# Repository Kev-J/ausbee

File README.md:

Overview
============

Architecture Using STM32 By Eirbot ENSEIRB-MATMECA.
This tool is provided for building automatically a complete STM32F project.

Licence
=============

See LICENCE file.

Usage
=============

- git clone the repository or download the snapshot of the last version.
- If you choose the git clone method, it is recommended to use a tagged version (git checkout vX.X).
- Configure your board (type "make help" for further informations).
- write your source code in Project/src (headers and source files).
- run "make"
- run "make program" for downloading your code into your device.

For further informations, please visit our wiki : https://github.com/Kev-J/ausbee/wiki

Features
=============

- FreeRTOS
- ST Std_Periph_Driver
- libausbee
- stm32flash

Dependencies
=============
* gperf
* flex
* bison
* libncurses-dev (for menuconfig)
* wget
* unzip
* tar
* stm32flash

Please note that this project is using many third party programs. Please ensure
that your setup have all the requirements before using them. For instance,
have a look to the [GCC arm embedded README](https://launchpadlibrarian.net/209775724/readme.txt)
and check that you have all the dependencies installed on your machine before
trying to compile anything.

Authors of the project
=============

Please see AUTHORS

Bugs, patch, requests
=============

https://github.com/Kev-J/ausbee
or
<ausbee@googlegroups.com>

Maintainer : Kevin JOLY <joly.kevin25@gmail.com>

Related to this project
=============

libausbee
-------------
https://github.com/Kev-J/libausbee

ausbee-hardware
-------------
https://github.com/Kev-J/ausbee-hardware

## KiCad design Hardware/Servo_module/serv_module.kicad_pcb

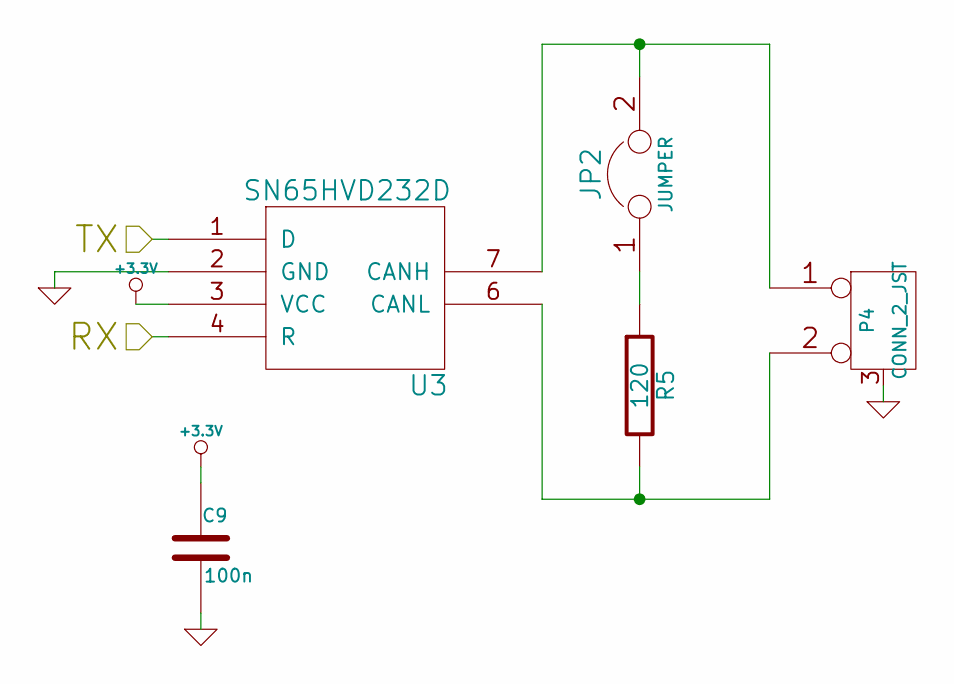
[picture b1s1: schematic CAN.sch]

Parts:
C9: 100n
JP2: JUMPER
P4: CONN_2_JST
R5: 120
U3: SN65HVD232D

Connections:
+3.3V: C9.1, U3.3 (VCC); also elsewhere on the board
/microcontroller/CAN_RX: U3.4 (R); also elsewhere on the board
/microcontroller/CAN_TX: U3.1 (D); also elsewhere on the board
GND: C9.2, P4.3, U3.2 (GND); also elsewhere on the board
unnamed: JP2.2, P4.1, U3.7 (CANH)
unnamed: JP2.1, R5.1
unnamed: P4.2 (PM), R5.2, U3.6 (CANL)

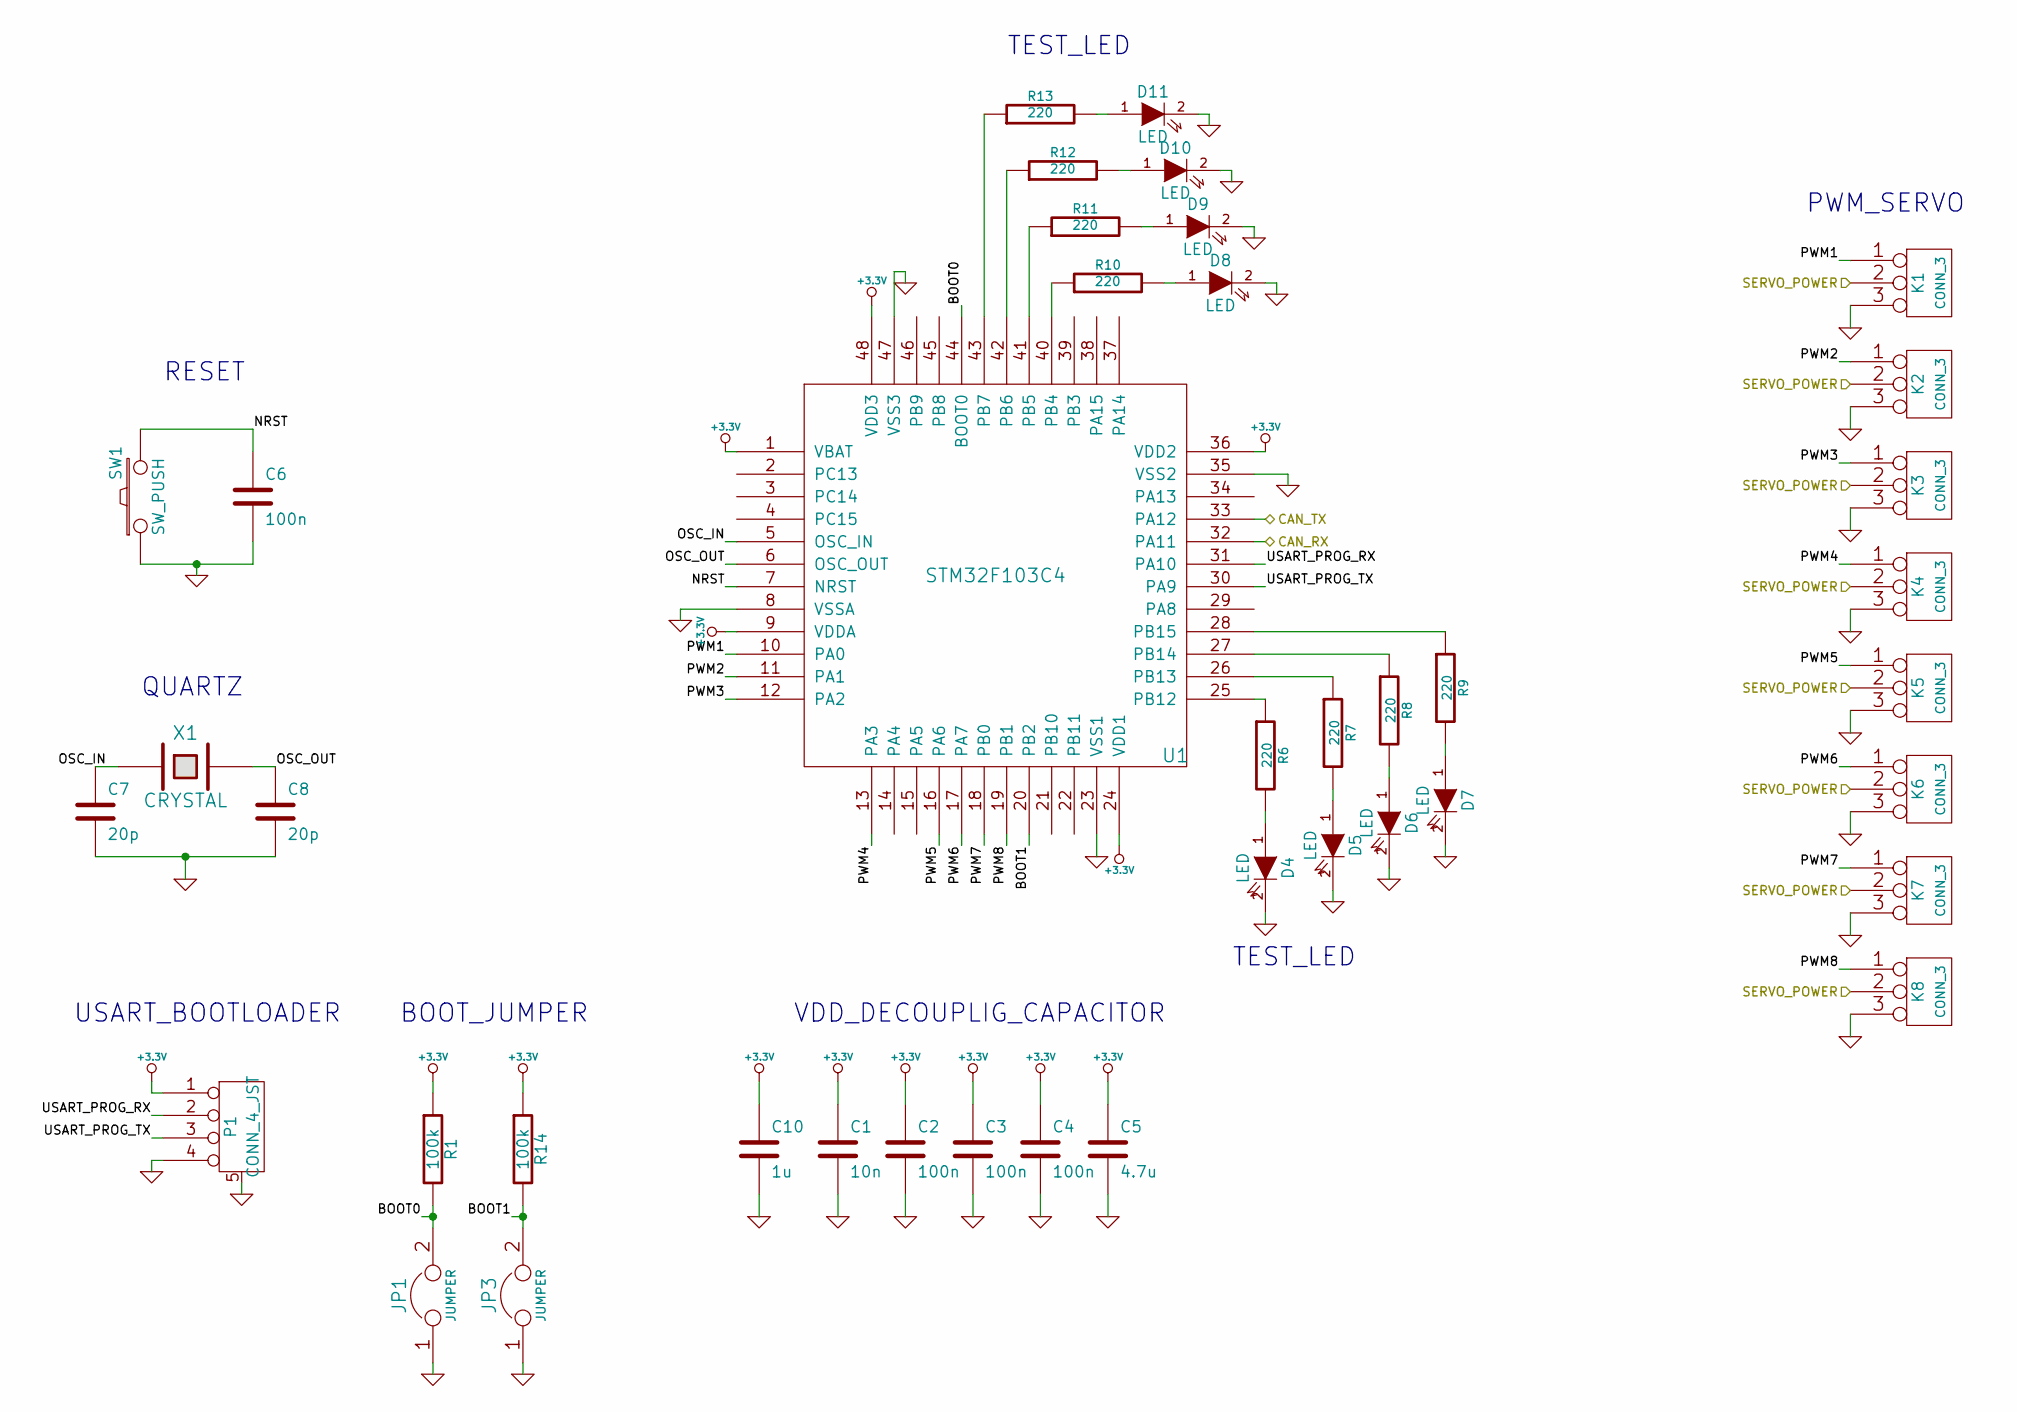
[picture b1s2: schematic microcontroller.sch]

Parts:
C1: 10n
C2, C3, C4, C6: 100n
C5: 4.7u
C7, C8: 20p
C10: 1u
D4, D5, D6, D7, D8, D9, D10, D11: LED
JP1, JP3: JUMPER
K1, K2, K3, K4, K5, K6, K7, K8: CONN_3
P1: CONN_4_JST
R1, R14: 100k
R6, R7, R8, R9, R10, R11, R12, R13: 220
SW1: SW_PUSH
U1: STM32F103C4
X1: CRYSTAL

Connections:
+3.3V: C1.1, C2.1, C3.1, C4.1, C5.1, C10.1, P1.1, R1.1, R14.1, U1.1 (VBAT), U1.9 (VDDA), U1.24 (VDD1), U1.36 (VDD2), U1.48 (VDD3); also elsewhere on the board
/microcontroller/BOOT0: JP1.2, R1.2, U1.44 (BOOT0)
/microcontroller/BOOT1: JP3.2, R14.2, U1.20 (PB2)
/microcontroller/CAN_RX: U1.32 (PA11); also elsewhere on the board
/microcontroller/CAN_TX: U1.33 (PA12); also elsewhere on the board
/microcontroller/NRST: C6.1, SW1.2, U1.7 (NRST)
/microcontroller/OSC_IN: C7.1, U1.5 (OSC_IN), X1.1
/microcontroller/OSC_OUT: C8.1, U1.6 (OSC_OUT), X1.2
/microcontroller/PWM1: K1.1, U1.10 (PA0)
/microcontroller/PWM2: K2.1, U1.11 (PA1)
/microcontroller/PWM3: K3.1, U1.12 (PA2)
/microcontroller/PWM4: K4.1, U1.13 (PA3)
/microcontroller/PWM5: K5.1, U1.16 (PA6)
/microcontroller/PWM6: K6.1, U1.17 (PA7)
/microcontroller/PWM7: K7.1, U1.18 (PB0)
/microcontroller/PWM8: K8.1, U1.19 (PB1)
/microcontroller/SERVO_POWER: K1.2 (PM), K2.2 (PM), K3.2 (PM), K4.2 (PM), K5.2 (PM), K6.2 (PM), K7.2 (PM), K8.2 (PM); also elsewhere on the board
/microcontroller/USART_PROG_RX: P1.2, U1.31 (PA10)
/microcontroller/USART_PROG_TX: P1.3, U1.30 (PA9)
GND: C1.2, C2.2, C3.2, C4.2, C5.2, C6.2, C7.2, C8.2, C10.2, D4.2 (K), D5.2 (K), D6.2 (K), D7.2 (K), D8.2 (K), D9.2 (K), D10.2 (K), D11.2 (K), JP1.1, JP3.1, K1.3, K2.3, K3.3, K4.3, K5.3, K6.3, K7.3, K8.3, P1.4, P1.5 (Shield), SW1.1, U1.8 (VSSA), U1.23 (VSS1), U1.35 (VSS2), U1.47 (VSS3); also elsewhere on the board
unnamed: D10.1 (A), R12.2
unnamed: D9.1 (A), R11.2
unnamed: D8.1 (A), R10.2
unnamed: D7.1 (A), R9.2
unnamed: D6.1 (A), R8.2
unnamed: D5.1 (A), R7.2
unnamed: D11.1 (A), R13.2
unnamed: R9.1, U1.28 (PB15)
unnamed: R8.1, U1.27 (PB14)
unnamed: R7.1, U1.26 (PB13)
unnamed: R6.1, U1.25 (PB12)
unnamed: R13.1, U1.43 (PB7)
unnamed: R12.1, U1.42 (PB6)
unnamed: D4.1 (A), R6.2
unnamed: R11.1, U1.41 (PB5)
unnamed: R10.1, U1.40 (PB4)

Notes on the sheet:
QUARTZ
USART_BOOTLOADER
BOOT_JUMPER
RESET
PWM_SERVO
VDD_DECOUPLIG_CAPACITOR
TEST_LED

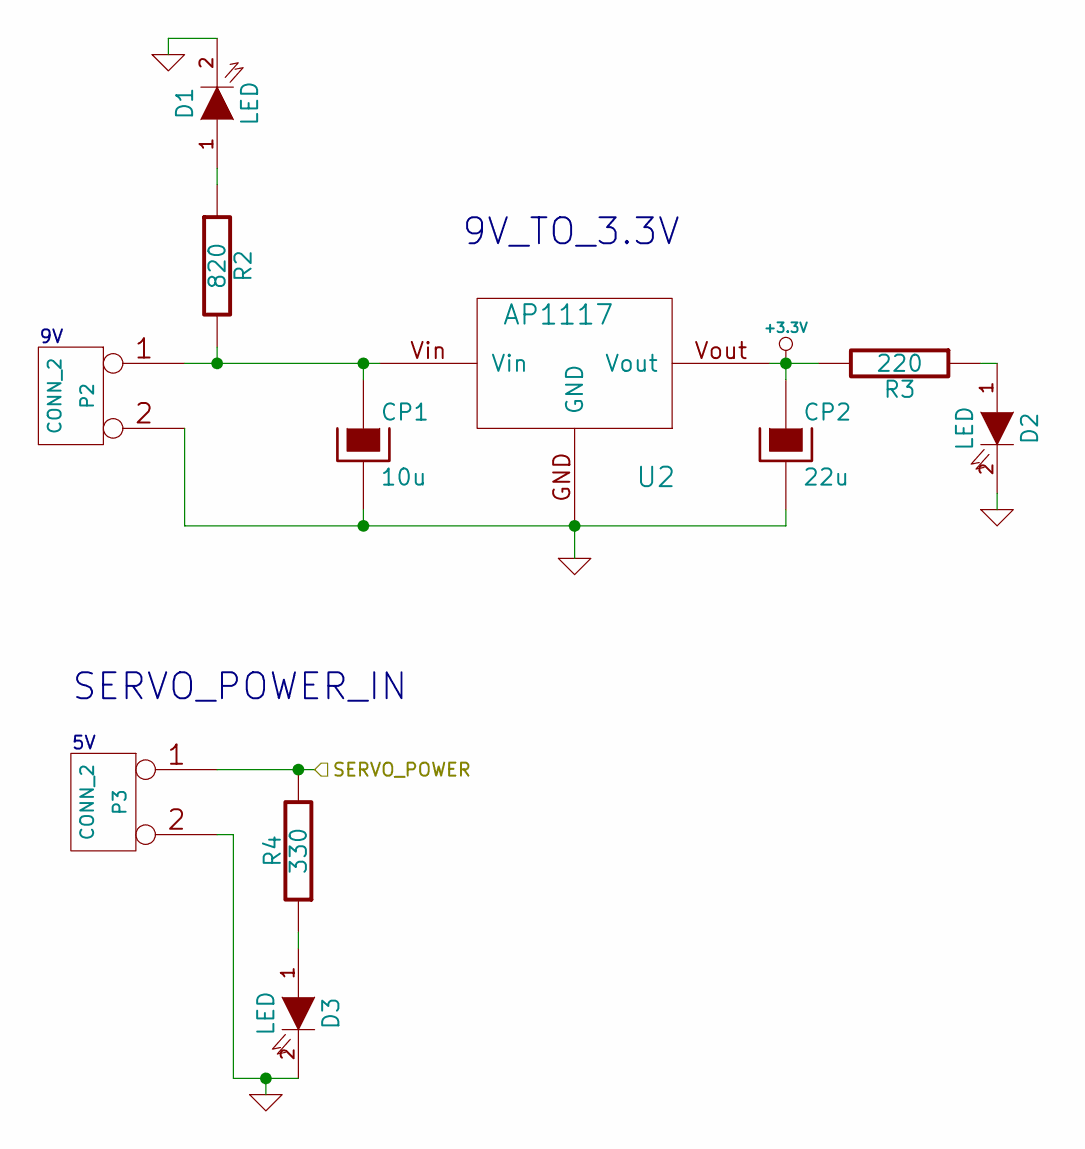
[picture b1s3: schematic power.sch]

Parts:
CP1: 10u
CP2: 22u
D1, D2, D3: LED
P2, P3: CONN_2
R2: 820
R3: 220
R4: 330
U2: AP1117

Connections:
+3.3V: CP2.1, R3.2, U2.Vout; also elsewhere on the board
/microcontroller/SERVO_POWER: P3.1, R4.2; also elsewhere on the board
GND: CP1.2, CP2.2, D1.2 (K), D2.2 (K), D3.2 (K), P2.2 (PM), P3.2 (PM), U2.GND; also elsewhere on the board
unnamed: D1.1 (A), R2.1
unnamed: D2.1 (A), R3.1
unnamed: D3.1 (A), R4.1
unnamed: CP1.1, P2.1, R2.2, U2.Vin

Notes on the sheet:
SERVO_POWER_IN
9V_TO_3.3V

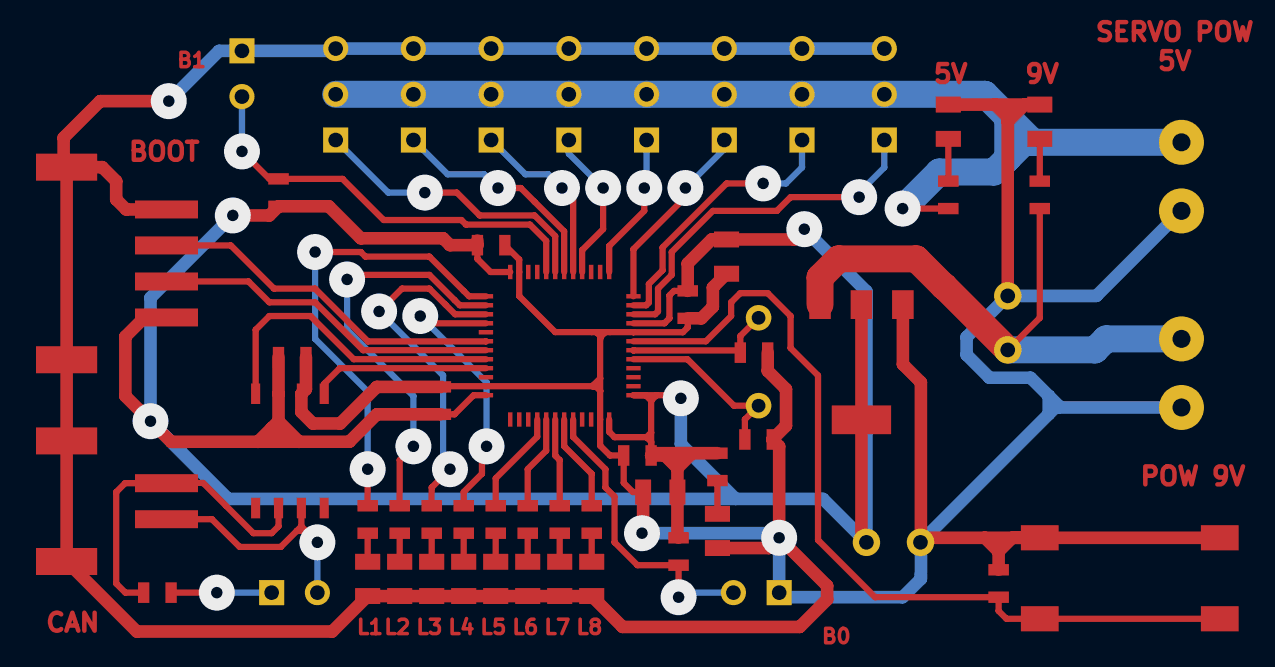
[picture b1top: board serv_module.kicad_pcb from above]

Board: 2 copper layers, 57 parts (0 on the bottom side), 43 nets.

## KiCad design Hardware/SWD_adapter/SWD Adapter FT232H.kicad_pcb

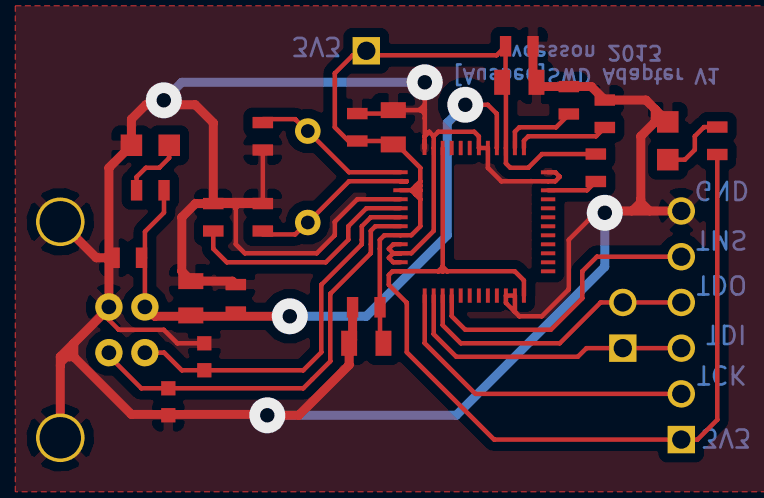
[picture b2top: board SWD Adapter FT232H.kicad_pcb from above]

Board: 2 copper layers, 27 parts (0 on the bottom side), 18 nets.

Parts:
C1, C2, C3, C4: C_0.1uF; SM0603
CP1, CP2, CP3, CP4: C_4.7uF; SM0805
C_Crystal1, C_Crystal2: C_27pF; SM0603
C_VBUS1: C_10nF; SM0603
C_VCCA1: C_0.1uF; SM0603
C_VCORE1: C_0.1uF; SM0603
D1, D2: ESDSUPPRESSOR; LED-0603
FT232H1: FT232H; FT232HLQFP
LED1: LED_Board_3V3; LED-0805
LED2: LED_USB_5V; LED-0805
P2: JUMPER; PIN_ARRAY_2X1
P3: CONN_JTAGSWD; PIN_ARRAY-6X1
Pinout_3V3: CONN_1; PIN_ARRAY_1
R_LED1, R_LED2: R; SM0603
R_REF1: R; SM0603
R_Reset1: R; SM0603
USB_CONN1: USB; USB_B
Xtal1: Xtal_12MHz; HC-49V

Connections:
/BOARD_3V3: FT232H1.12, FT232H1.24, FT232H1.46, P3.1, R_LED1.1
/TCK: FT232H1.13, P3.2
/TDI: FT232H1.14, P2.1, P3.3
/TDO: FT232H1.15, P2.2, P3.4
/TMS: FT232H1.16, P3.5
/VBUS_5V: C3.1, CP3.1, C_VBUS1.1, FT232H1.40, R_LED2.1, USB_CONN1.1
/VCCD_3V3: C1.1, C2.1, C4.1, CP1.1, CP2.1, CP4.1, FT232H1.3, FT232H1.8, FT232H1.39, Pinout_3V3.1, R_Reset1.1
GND: C1.2, C2.2, C3.2, C4.2, CP1.2, CP2.2, CP3.2, CP4.2, C_Crystal1.2, C_Crystal2.2, C_VBUS1.2, C_VCCA1.2, C_VCORE1.2, D1.2, D2.1, FT232H1.4, FT232H1.9, FT232H1.10, FT232H1.11, FT232H1.22, FT232H1.23, FT232H1.35, FT232H1.36, FT232H1.41, FT232H1.42, FT232H1.47, FT232H1.48, LED1.2, LED2.2, P3.6, R_REF1.2, USB_CONN1.4, USB_CONN1.5, USB_CONN1.6
unnamed: C_VCORE1.1, FT232H1.38
unnamed: FT232H1.34, R_Reset1.2
unnamed: FT232H1.5, R_REF1.1
unnamed: C_VCCA1.1, FT232H1.37
unnamed: D2.2, FT232H1.6, USB_CONN1.2
unnamed: D1.1, FT232H1.7, USB_CONN1.3
unnamed: LED2.1, R_LED2.2
unnamed: LED1.1, R_LED1.2
unnamed: C_Crystal1.1, FT232H1.1, Xtal1.1
unnamed: C_Crystal2.1, FT232H1.2, Xtal1.2

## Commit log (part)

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2013-10-22 [HARDWARE] routing
2013-10-25 [HARDWARE][SERVO_MODULE] Schematic
2013-10-25 [HARDWARE][SWD_adapter]schema+routage
2013-10-25 [HARDWARE][SWD_Adapter]routage a verifier
2013-10-26 [HARDWARE][SWD_Adapter]Ajout des plans de masse
2013-10-27 [HARDWARE][SERVO_MODULE] Board legend
2013-10-27 [HARDWARE][SERVO_MODULE] Add board .brd
2013-11-04 [HARDWARE][SWD_Adapter]Routage: capa de decouplage plus proches des pins
2013-11-05 [HARDWARE][SERVO_MODULE] Add GND plane on board
2013-11-05 [HARDWARE][SWD_Adapter]correction de routage
2013-11-07 Remove build tool CMAKE files for kconfig-frontends
2013-11-08 [HARDWARE][SERVO_MODULE] Typon files correction
2013-11-08 [HARDWARE][SERVO_MODULE] Final schematic. Change some footprint and line width
2013-11-15 [SOFTWARE] PID creation
2013-11-22 [SOFTWARE] Add error message when no configuration file has been found
2013-11-22 [SOFTWARE] Define a new structure of building project
2013-11-22 [SOFTWARE] Rearrange all directory architecture
2013-11-22 [Software]Remove files with ~
2013-11-22 [SOFTWARE] Add StdPeriph drivers for STM32F4xx and remove lib directory
2013-11-23 [SOFTWARE] Remove a swp file
2013-11-23 start generic class CAN
2013-11-23 [SOFTWARE] Change the way to select the device
2013-11-23 slight modif on can.h can.c
2013-11-23 [SOFTWARE][LIBAUSBEE] Reorganise directories and remove autotools
2013-11-24 constructor of class CAN
2013-11-24 [SOFTWARE][LIBAUSBEE] Add libausbee's makefile
2013-11-24 [SOFTWARE] Enable the user to call make clean or make dirclean when no config has been found
2013-11-24 [SOFTWARE] Add stm32flash support
2013-11-24 [SOFTWARE][LIBAUSBEE] Rename examples in tools and make ausbee-lidar-viewer compiling with CMake
2013-11-24 [SOFTWARE][DOC] Init files
2013-11-24 [SOFTWARE] Add make help rule
2013-11-24 [SOFTWARE] fix config.mk mistake about .config loading
2013-11-24 [SOFTWARE] startup script test
2013-11-26 [SOFTWARE] Enable g++ optimisations
2013-11-26 [SOFTWARE] Add some infos
2013-11-26 [SOFTWARE] Change obj dependancies mechanism and make use of FreeRTOS being optionnal
2013-11-26 [SOFTWARE] Keep comments when preprocessing linker script
2013-11-26 [SOFTWARE] Move FreeRTOS to Operating_Systems directory
2013-11-26 [SOFTWARE] TODO
2013-11-26 [SOFTWARE] Make Cortex-M4 compiling
2013-11-27 [SOFTWARE] Add CM3 syscalls
2013-11-29 [SOFTWARE][DOC] Rename the stdperiph correct name
2013-11-29 [SOFTWARE] Add platform directory
2013-11-30 [SOFTWARE] Change makefile order
2013-11-30 [SOFTWARE] Add stm32 header to syscalls
2013-11-30 [SOFTWARE] Reorganise Kconfig and set debug support
2013-11-30 [SOFTWARE] Add led support in libausbee
2013-11-30 [SOFTWARE] Remove main_board_v0 config
2013-11-30 [SOFTWARE] Make the assert system dependant to DEBUG macro
2013-11-30 [SOFTWARE] Add crystal oscillator macro
2013-11-30 [SOFTWARE][PLATFORM] Add platform.c for ausbee_main_board_v0.1
2013-11-30 [SOFTWARE] Fix header name
2013-12-03 [SOFTWARE][LIBAUSBEE] Remove led module
2013-12-03 [SOFTWARE] Improve clean goals
2013-12-03 [SOFTWARE][SYSTEM-CM4] Remove a bracket
2013-12-03 [SOFTWARE][SYSTEM-CM4] Add optimisation
2013-12-03 [SOFTWARE] TODO list
2013-12-03 [SOFTWARE][PLATFORMS] Fix clean goals
2013-12-03 [SOFTWARE][DOC] Add STM32F4xx_StdPeriph doxyfile
2013-12-03 [SOFTWARE] Enable FPU
2013-12-07 [SOFTWARE][OS] Set NONE the first choice
2013-12-07 [SOFTWARE] Fix syscalls
2013-12-08 slight modification on platform for CAN
2013-12-08 [SOFTWARE] Make the L298 available in Kconfig
2013-12-08 [SOFTWARE] update TODO
2013-12-08 [SOFTWARE] Add CAN init function to the header file
2013-12-08 [Software]add servo module platform
2013-12-08 [SOFTWARE] Add init motor 2 and modify init motor1
2013-12-08 [SOFTWARE] Enable the use of FPU for F4
2013-12-08 [SOFTWARE] Add library servo in libausbee
2013-12-12 [SOFTWARE] Change STM32F4xx stdperiph name
2013-12-14 [SOFTWARE]Update kconfig for stm32f10x libraries
2013-12-20 add misc in Kconfig
2013-12-20 [SOFTWARE] Modify USART config on platform.c
2013-12-20 [SOFTWARE]remove .o files
2013-12-20 [SOFTWARE]Update servo module platform
2013-12-27 schematic power card
2013-12-31 modification on power board: add relay and fuse
2014-01-09 add MOS instead of bipolar and change fuse footprint
2014-01-10 [SOFTWARE]Add example folder + update servo module platform
2014-01-10 [SOFTWARE]Remove main.h in Robot Code Example
2014-01-10 [SOFTWARE] Add Doxyfile for documentation
2014-01-12 [SOFTWARE] Corrected spelling mistakes + removed unwanted tabs
2014-01-13 [SOFTWARE][QUADRAMP] Drawing generated speed and acceleration
2014-01-27 add GPIO in platform
2014-01-27 Power board V2, adaptator GPIO
2014-01-28 modif on .mk, platform, and servo for portability
2014-01-28 [SOFTWARE][LIBAUSBEE] Remove asserv and add Control engineering functions
2014-01-28 [SOFTWARE][LIBAUSBEE] Doc
2014-01-28 add pwm init in platform
2014-01-29 [SOFTWARE][LIBAUSBEE] Add lidar support and make it compliant with the lidar_viewer tool
2014-02-06 [SOFTWARE]Add SPI sources in configuration files
2014-02-07 [SOFTWARE]Add programmer select in menuconfig
2014-02-08 [SOFTWARE]Update f4discovery platform + f4discovery example code
2014-02-08 [SOFTWARE]Update F4Discovery platform and example
2014-02-28 [SOFTWARE]Add AX12 in libausbee
2014-03-15 remove include of platform.h in ax12
2014-03-16 removed can from libausbee and slight modif in l298 driver
2014-03-21 add other usart in platform init and remove lidar.h include from lidar.h
2014-04-05 add define in platform.h
2014-04-12 [TEXT] Adding a .gitignore in Software
2014-04-13 Adding Command line interface (Beta)
2014-04-13 Tool to plot encoder value with PID
2014-04-13 [SOFT] Adding encoder to libausbee
2014-04-13 [SOFT] Adding a first control system manager
2014-04-13 [SOFT][LIBAUSBEE] Update encoder module
2014-04-16 [SOFT] Emptying project's sources to create a separate repo for it
2014-04-19 [SOFT] Fixed lidar_viewer compilation
2014-04-26 [SOFTWARE] Subdirectories now possible in projects
2014-04-27 [SOFT] csm is no longer dependent on the type of controller used (such as a pid)
2014-04-27 [SOFT] Creating a debug_printf macro for debugging purpose
2014-04-27 [SOFT] Fixed int32_t in printf warning
2014-04-28 [SOFT] Starting a quest against warnings.
2014-04-28 [SOFT] Encoder1 now working!
2014-04-28 [SOFT] Removed binary file + ignoring them
2014-05-01 [SOFT] Adding a tool to plot pid value
2014-05-01 [SOFT] Generic ploting tool
2014-05-01 Uniformisation of platform functions
2014-05-02 [SOFT] pid: new function to change reference
2014-05-02 [SOFT] Ploting pid values for both motors
2014-05-03 [SOFT] Plotting robot distance
2014-05-09 [SOFT] Clock init in separate function
2014-05-09 [SOFT] plotting tool: can print floats
2014-05-10 [SOFT] plotting tool: printing any size of data sample
2014-05-10 [SOFT] plotting tool: highlighting current robot position
2014-05-11 [SOFT] control system now gets the reference as param
    A new function is used to get the measure.
    Controllers now take error as params rather than reference.
2014-05-14 [SOFT] intergers replaced by floats in control system
2014-05-14 [SOFT] pid: function naming standardization + better interface
2014-05-18 [SOFT] cs: adding a diff filter on measure
2014-05-18 [SOFT][DOC] Adding some missing doc
2014-05-18 [SOFT] plotting tool: fixed y axe data range
2014-05-24 [SOFT] movement_generation: removed, replaced by quadramp filter
2014-05-24 remove other debug printf in platform
2014-05-24 [SOFT] diff: fixed doc
2014-05-25 [SOFT] pid: coeffs are floats
2014-05-25 [SOFT] plotting tool: better parameters
2014-05-26 [SOFT] pid: adding setter and getters for pid parameters
2014-09-23 Remove Libraries dir
2014-09-23 Remove documentation directory
2014-09-23 Make the ausbee_main_board platform compliant with last commit
2015-05-03 Removing misplaced file
2015-05-08 Ausbee platform: now supporting encoders with quadrature
2015-05-08 Using latest libausbee-1.0 that supports encoders with quadrature
2015-05-21 add multiproject support for menuconfig
2015-05-21 add multiproject compilation. Need to put object files in a project subdirectory
2015-05-21 generate project object file in Output/Project directory
2015-05-21 generate ausbee object file in project output directory
2015-05-22 generate platform object files in projet output directory
2015-05-22 add the ability to use system path for toolchain binaries
2015-05-26 Fix stm32f10x_stdperiph path
2015-05-26 Add a changelog
2015-05-26 Add include dir to .gitignore rules
2015-05-26 Change the toolchain extracted path into build subdirectory
2015-05-26 Remove old ld file from .gitignore
2015-05-27 new indentation of Kconfig
2015-06-09 Add custom platforms Kconfig to general makemenuconfig
2015-06-10 fix comments
2015-06-11 move custom platforms config from Makefile to menconfig
2015-06-11 Add subdirectories of Project in .gitignore
2015-06-11 Add GPLv3
2015-06-12 fix displayed size
2015-06-12 add program rule for avrdude
2015-06-14 add ability to get libausbee from git
2015-06-14 too much cleaning !
2015-06-17 path for include inside Kconfig
2015-06-22 handle custom platform and set correct ram and flash values for official platforms
2015-06-24 Add AUTHORS file and improve README.md
2015-06-24 Add some extra informations under Dependencies section in README.md
2015-06-24 Handle FreeRTOS config in Kconfig
2015-07-01 add xmega128a1 support
2015-07-01 force usb if isp mkII is selected
2015-07-02 add .config as dependancy to all object & link generation
2015-07-02 generate dependancy files for packages
2015-07-02 generate dependancy files for system-cmX
2015-07-02 fix generated path
2015-07-03 fix dependancy generation for make clean rule
2015-07-04 fix Kconfig for programming baudrate & interface
2015-07-04 avr port need a freeRTOS version >=8.0.0
2015-07-08 Fix file dependancies in makefiles
2015-07-17 remove cast for MAX_PRIORITIES. The cast is useless(?) and break build with FreeRTOS v>=8.0.0
2015-07-19 Don't break FreeRTOS v7 build
2015-07-25 Add some directions to ensure that the correct clock of the MCU is selected
2015-10-19 Download all package before starting to build
2015-10-19 use global operating system include list variable
2015-10-19 fix makefile script for host target
2015-10-20 Rewrite code for simulation build. Better integration into ausbee
2015-10-21 Fix multiproject bug ; Add script for creating projects
2015-10-21 fix colored echo
2015-10-21 remove pkg-generic-old
2015-10-21 Add chip-info and debugging
2015-10-25 fix output file name
2015-10-25 add new define for TARGET/SIM differentiation
2016-03-10 add gnu99 when compiling in sim mode (for old gcc)
2016-03-23 add eventÃ_groups freertos modules
2016-05-20 [PLATFORMS] Add stm32f7discovery platform
2016-05-20 [PLATFORMS] Fix stm32f4discovery built_print call
2016-05-23 [PLATFORMS] Update stm32f7discovery platform
2016-05-23 [SYSTEM][CM7] Fix typo
2016-05-24 [TOOLCHAIN] Switch to gcc-arm-embedded 5-2016-q1 for default configuration
2016-05-24 Ignore downloads directory
2016-05-24 [PACKAGES] Remove debug print
2016-05-24 Fix CM0+ macro in config.mk
2016-05-31 [PACKAGES] Add stm32_usb_device_library package
2016-05-31 [SYSTEM][CM0Plus] Add end of stack symbols in linker script
2016-06-01 [PLATFORM][STM32F7DISCOVERY] Add menu
2016-06-01 Print size after link
2016-06-09 [PLATFORM][STM32F7DISCOVERY] Add storage drivers
2016-06-09 Add semihosting support for CM7 and OpenOCD
2016-06-26 Add a way to auto-discover package source files. Useful if you are working on a separated branch with a different source file list
2017-06-13 fix build with gperf 3.1
2017-06-13 Gperf 3.1 fix broke build for Gperf 3.0.x
2017-06-15 create output directory before generating link
2017-06-15 fix find on mac
2017-06-15 add gnu99 as default
2017-06-18 Add freeRTOS POSIX port in freertos makefile
2017-10-25 Add new freeRTOS linux port
2018-04-13 add Kconfig option for xmega
2018-04-13 fix avr-ld usage for step board
2018-09-30 Add exit command to openocd command line
2018-11-10 various fixes written during the 2018 robotic cup
2018-11-10 autogenerate git header
2018-12-08 missing file
2019-04-19 Add system for M0 et L4
